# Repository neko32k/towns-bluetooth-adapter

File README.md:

# FM TOWNS Bluetooth Adapter (towns-bluetooth-adapter)

This repository contains firmware, circuit diagrams, and documentation for a Bluetooth input adapter for FM TOWNS, using Adafruit Feather nRF52840. The goal is to enable modern Bluetooth keyboards, mice, and controllers to behave as HID devices for FM TOWNS systems.

このリポジトリは、Adafruit Feather nRF52840 を使用して FM TOWNS に Bluetooth 入力を追加するためのファームウェア、回路図、手順書をまとめたものです。Bluetooth キーボード／マウス／コントローラを FM TOWNS 側で HID として使えるようにすることを目標とします。

Disclaimer / 免責事項
- This project is an independent hobby project and is NOT affiliated with or endorsed by the FM TOWNS trademark owner or any commercial entity.
- 本プロジェクトは個人の趣味プロジェクトです。FM TOWNS の商標所有者や企業とは関係ありません。回路や接続による機器の故障や損害について作者は責任を負いません。実施は自己責任でお願いします。

Repository contents / 目次
- /arduino — Arduino スケッチ
- /kicad — KiCad プロジェクト（回路図・PCB）  
- /assets — 写真・動画・GIF  
- LICENSE — ライセンス（MIT）  

Requirements / 前提
- Adafruit Feather nRF52840 Express (or compatible)  
- FM TOWNS with accessible 5V power pin  
- Bluetooth input devices for testing

Companion blog / ブログ
- Project blog and notes: https://www.nk3-dev.net/  

Dependencies / 依存関係
This repository vendors `CircularQueue` (renamed to `CircularQueue.h`) from Francis‑Magallanes/CircularQueue.  
License: MIT — included in `licenses/CircularQueue_LICENSE.txt`.

本プロジェクトは `CircularQueue`（`CircularQueue.h` として同梱）を使用しています。上流は MIT ライセンスです（`licenses/CircularQueue_LICENSE.txt` を参照）。  
Included vendored file path: `arduino/bt_device/CircularQueue.h`

Affiliate disclosure / アフィリエイト表記
- Some links in this repository or the companion blog may be affiliate links (Amazon.co.jp Associate). 
- 本リポジトリおよび関連ブログには Amazon.co.jp 等のアフィリエイトリンクが含まれる場合があります。

License / ライセンス
This project is licensed under the MIT License — see the LICENSE file for details.  
本プロジェクトは MIT ライセンスで配布します。詳細は LICENSE を参照してください。

Author / 作者
- GitHub: neko32k  
- Year / 年: 2026

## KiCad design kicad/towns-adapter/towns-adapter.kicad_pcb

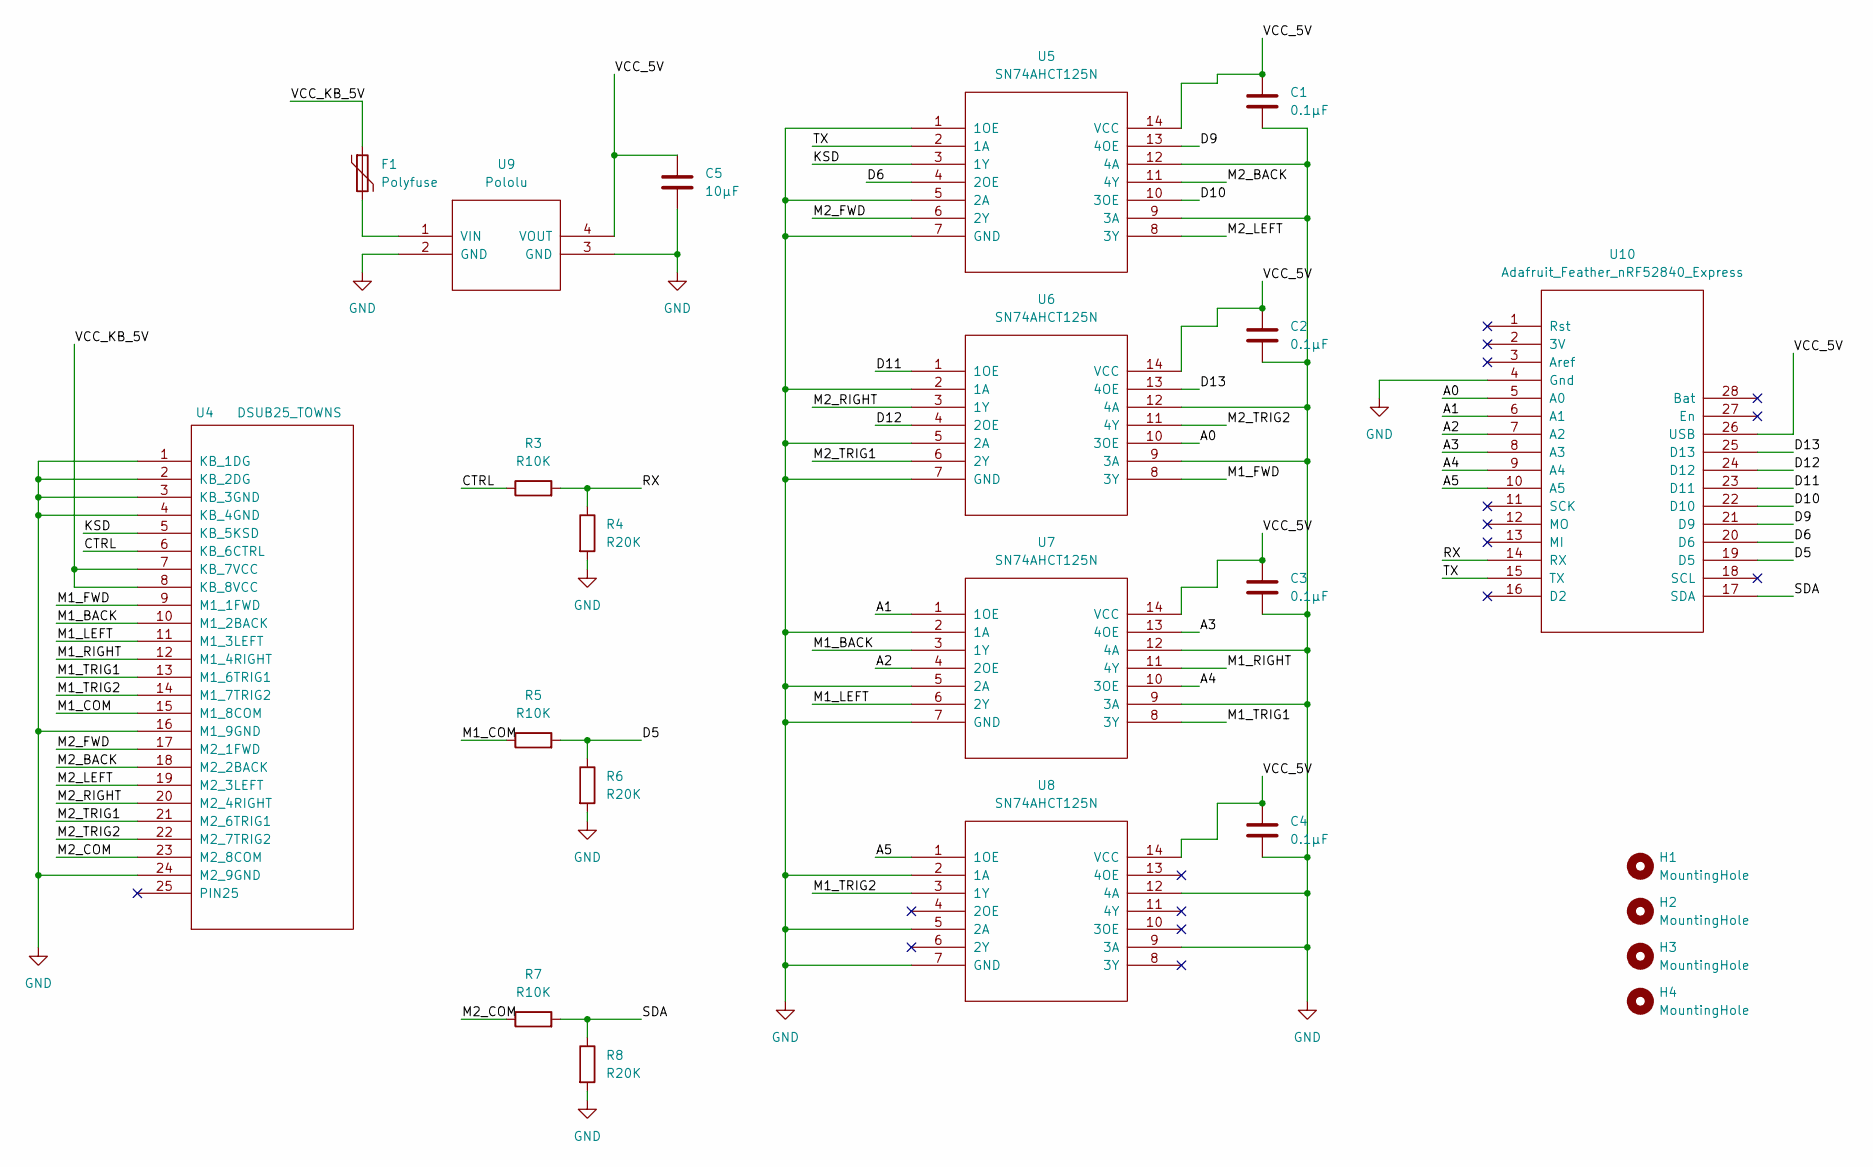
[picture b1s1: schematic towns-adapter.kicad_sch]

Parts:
C1, C2, C3, C4: 0.1μF; R_Axial_DIN0204_L3.6mm_D1.6mm_P5.08mm_Horizontal
C5: 10µF; CIP_CAPACITOR_C_1206_3216Metric_Pad1.33x1.80mm_HandSolder
F1: Polyfuse; R_Axial_DIN0204_L3.6mm_D1.6mm_P5.08mm_Horizontal
H1, H2, H3, H4: MountingHole; MountingHole_3.2mm_M3
R3, R5, R7: R10K; R_Axial_DIN0204_L3.6mm_D1.6mm_P7.62mm_Horizontal
R4, R6, R8: R20K; R_Axial_DIN0204_L3.6mm_D1.6mm_P7.62mm_Horizontal
U4: DSUB25_TOWNS; MODULE
U5, U6, U7, U8: SN74AHCT125N; MODULE
U9: Pololu; MODULE
U10: Adafruit_Feather_nRF52840_Express; MODULE

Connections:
/A0: U6.10 (3OE), U10.5 (A0)
/A1: U7.1 (1OE), U10.6 (A1)
/A2: U7.4 (2OE), U10.7 (A2)
/A3: U7.13 (4OE), U10.8 (A3)
/A4: U7.10 (3OE), U10.9 (A4)
/A5: U8.1 (1OE), U10.10 (A5)
/CTRL: R3.1, U4.6 (KB_6CTRL)
/D5: R5.2, R6.1, U10.19 (D5)
/D6: U5.4 (2OE), U10.20 (D6)
/D9: U5.13 (4OE), U10.21 (D9)
/D10: U5.10 (3OE), U10.22 (D10)
/D11: U6.1 (1OE), U10.23 (D11)
/D12: U6.4 (2OE), U10.24 (D12)
/D13: U6.13 (4OE), U10.25 (D13)
/KSD: U4.5 (KB_5KSD), U5.3 (1Y)
/M1_BACK: U4.10 (M1_2BACK), U7.3 (1Y)
/M1_COM: R5.1, U4.15 (M1_8COM)
/M1_FWD: U4.9 (M1_1FWD), U6.8 (3Y)
/M1_LEFT: U4.11 (M1_3LEFT), U7.6 (2Y)
/M1_RIGHT: U4.12 (M1_4RIGHT), U7.11 (4Y)
/M1_TRIG1: U4.13 (M1_6TRIG1), U7.8 (3Y)
/M1_TRIG2: U4.14 (M1_7TRIG2), U8.3 (1Y)
/M2_BACK: U4.18 (M2_2BACK), U5.11 (4Y)
/M2_COM: R7.1, U4.23 (M2_8COM)
/M2_FWD: U4.17 (M2_1FWD), U5.6 (2Y)
/M2_LEFT: U4.19 (M2_3LEFT), U5.8 (3Y)
/M2_RIGHT: U4.20 (M2_4RIGHT), U6.3 (1Y)
/M2_TRIG1: U4.21 (M2_6TRIG1), U6.6 (2Y)
/M2_TRIG2: U4.22 (M2_7TRIG2), U6.11 (4Y)
/RX: R3.2, R4.1, U10.14 (RX)
/SDA: R7.2, R8.1, U10.17 (SDA)
/TX: U5.2 (1A), U10.15 (TX)
/VCC_5V: C1.1, C2.1, C3.1, C4.1, C5.1, U5.14 (VCC), U6.14 (VCC), U7.14 (VCC), U8.14 (VCC), U9.4 (VOUT), U10.26 (USB)
/VCC_KB_5V: F1.1, U4.7 (KB_7VCC), U4.8 (KB_8VCC)
GND: C1.2, C2.2, C3.2, C4.2, C5.2, R4.2, R6.2, R8.2, U4.1 (KB_1DG), U4.2 (KB_2DG), U4.3 (KB_3GND), U4.4 (KB_4GND), U4.16 (M1_9GND), U4.24 (M2_9GND), U5.1 (1OE), U5.5 (2A), U5.7 (GND), U5.9 (3A), U5.12 (4A), U6.2 (1A), U6.5 (2A), U6.7 (GND), U6.9 (3A), U6.12 (4A), U7.2 (1A), U7.5 (2A), U7.7 (GND), U7.9 (3A), U7.12 (4A), U8.2 (1A), U8.5 (2A), U8.7 (GND), U8.9 (3A), U8.12 (4A), U9.2 (GND), U9.3 (GND), U10.4 (Gnd)
unnamed: F1.2, U9.1 (VIN)

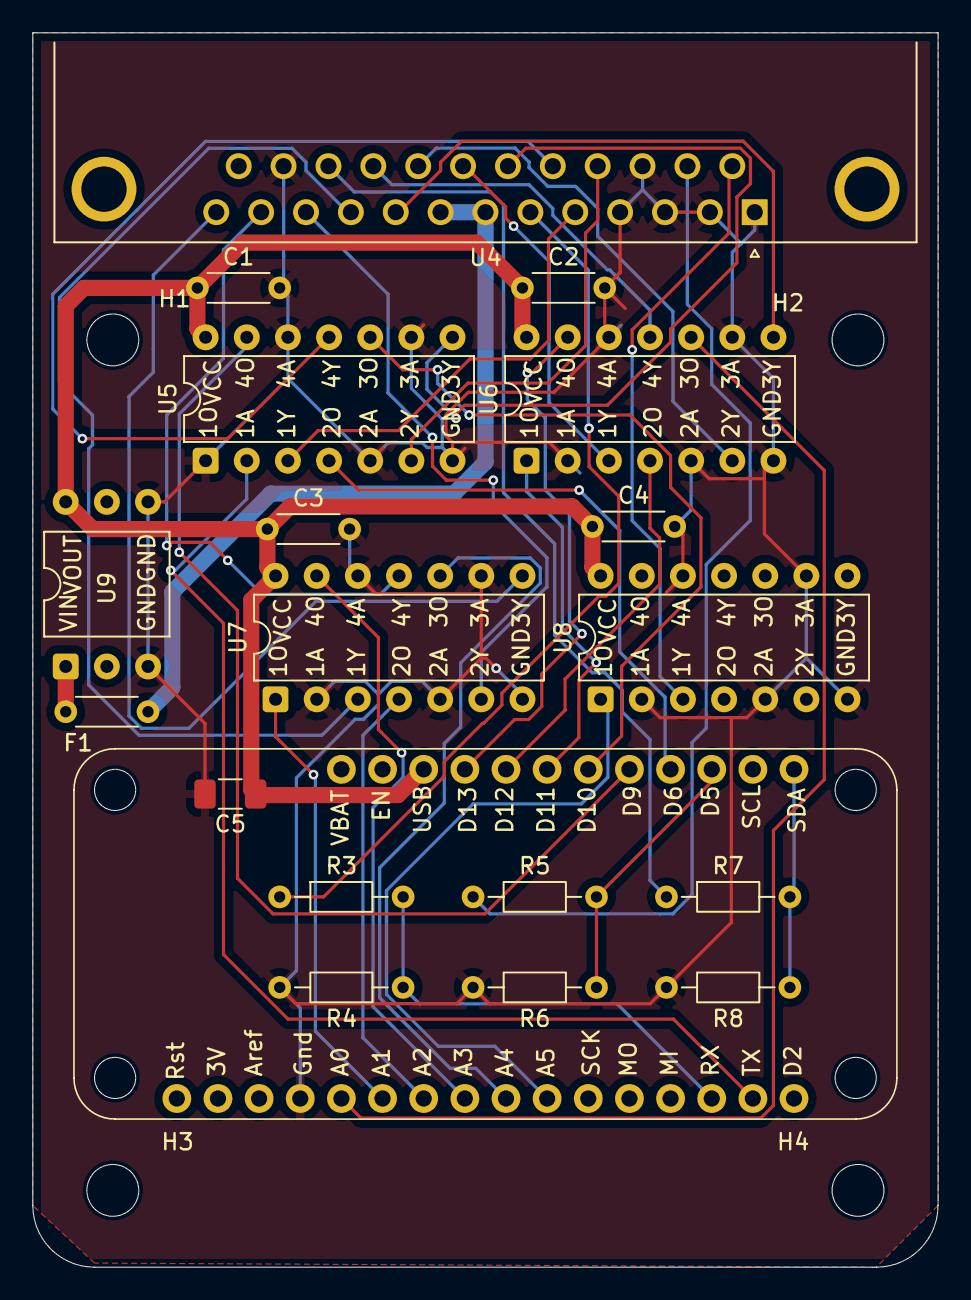
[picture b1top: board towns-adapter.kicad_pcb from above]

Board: 2 copper layers, 55.9 x 76.2 mm, 23 parts (0 on the bottom side), 36 nets.

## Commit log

2026-01-31 v0.6.0 — initial public snapshot: firmware, KiCad
2026-01-31 Update README.md with corrected directory paths.
2026-01-31 Update README.md with new content
2026-02-04 Add funding information for GitHub
